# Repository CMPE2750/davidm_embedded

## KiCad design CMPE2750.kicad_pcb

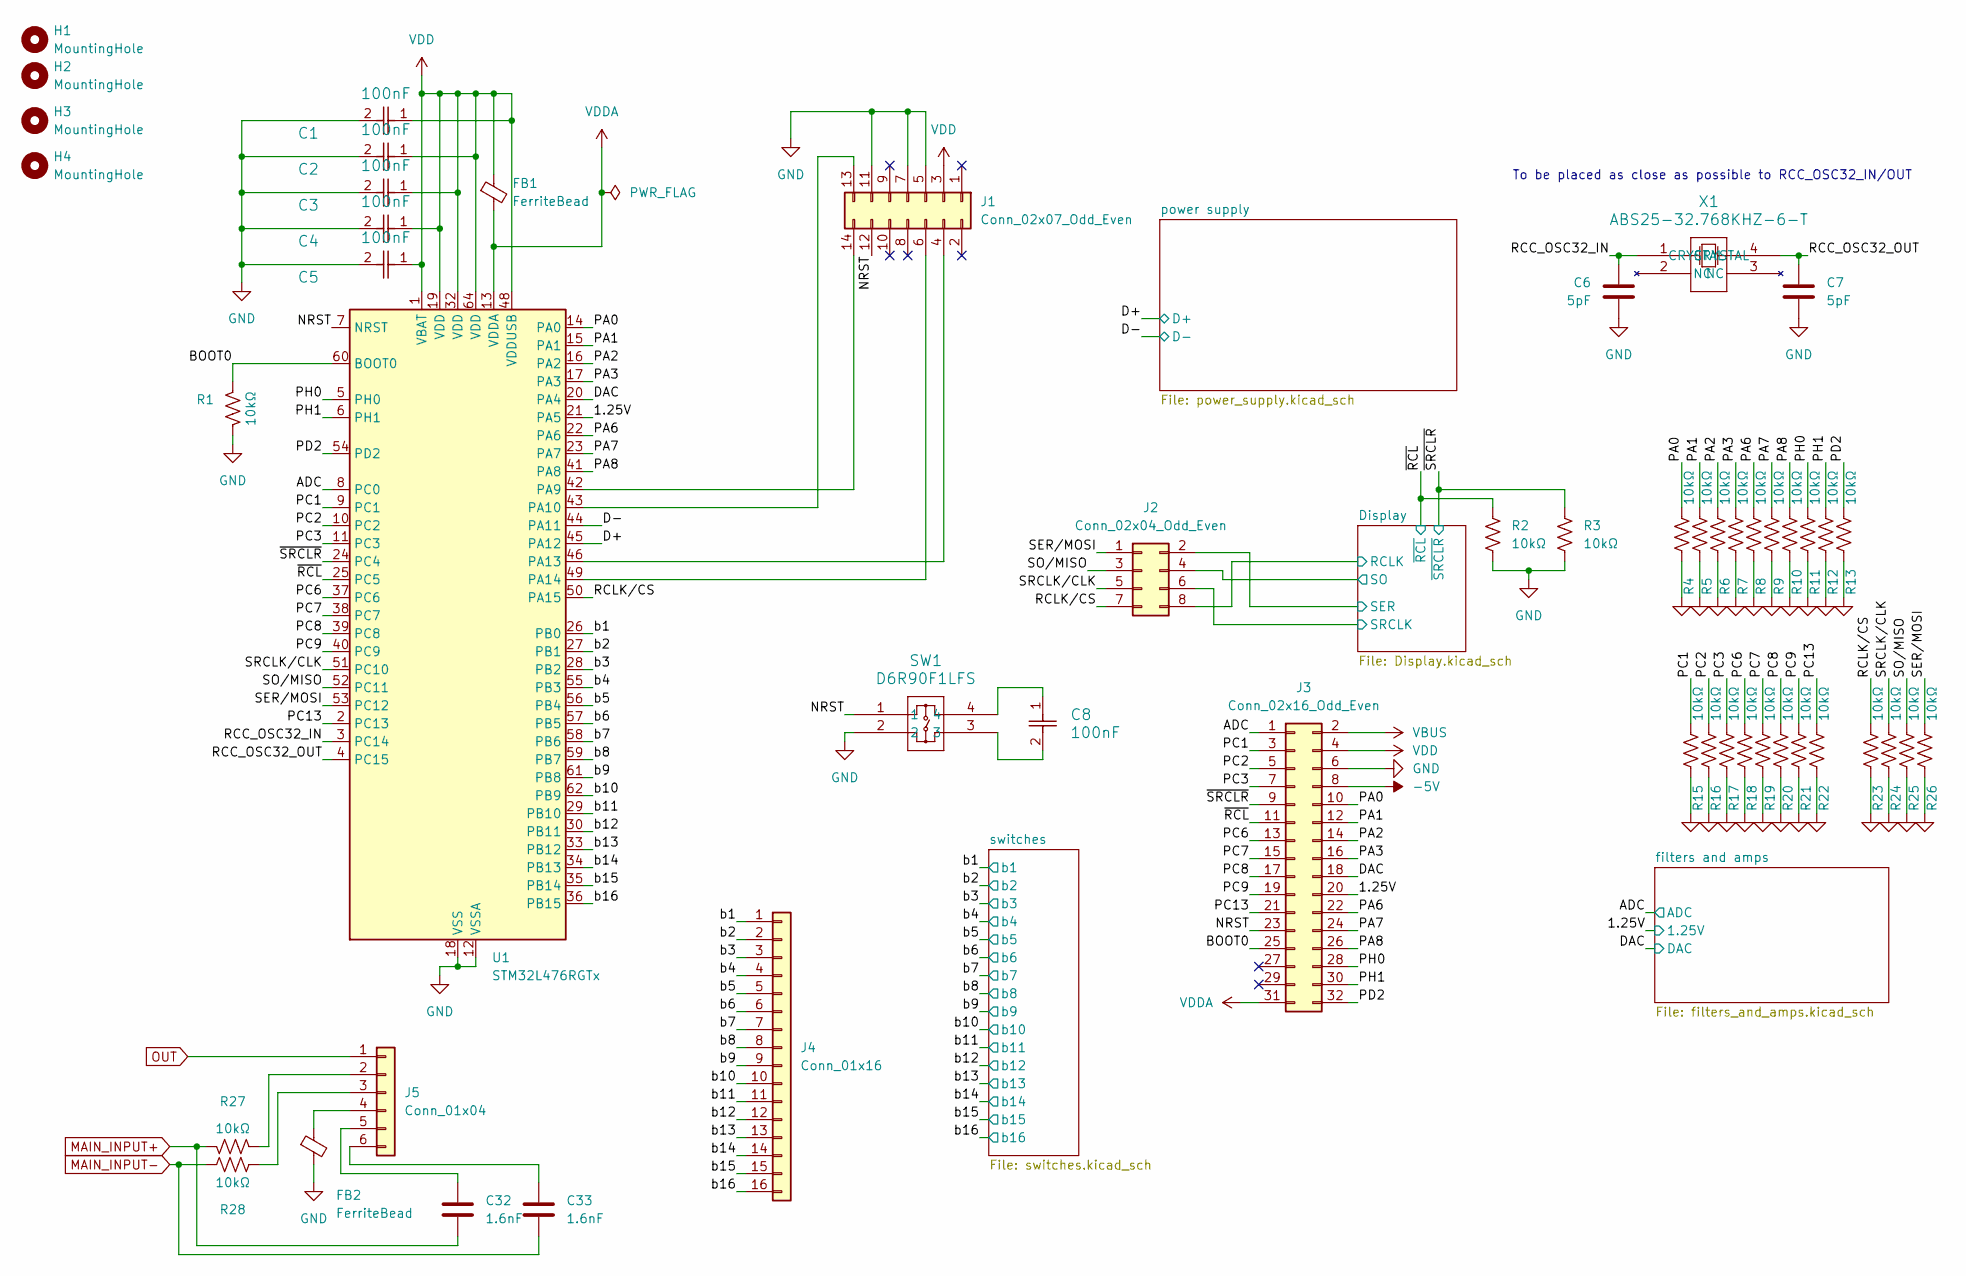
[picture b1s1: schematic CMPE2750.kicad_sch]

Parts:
C1, C2, C3, C4, C5, C8: 100nF; C_0402_1005Metric
C6, C7: 5pF; C_0402_1005Metric
C32, C33: 1.6nF; C_0805_2012Metric
FB1, FB2: FerriteBead; L_0603_1608Metric
H1, H2, H3, H4: MountingHole; MountingHole_3.2mm_M3
J1: Conn_02x07_Odd_Even; CONN_FTSH-107-01-F-DV-K-P-TR_SAI
J2: Conn_02x04_Odd_Even; PinHeader_2x04_P2.54mm_Vertical
J3: Conn_02x16_Odd_Even; PinHeader_2x16_P2.54mm_Vertical
J4: Conn_01x16; PinHeader_1x16_P2.54mm_Vertical
J5: Conn_01x04; PinHeader_1x06_P2.54mm_Vertical
R1, R2, R3, R4, R5, R6, R7, R8, R9, R10, R11, R12, R13, R15, R16, R17, R18, R19, R20, R21, R22, R23, R24, R25, R26, R27, R28: 10kΩ; R_0402_1005Metric
SW1: D6R90F1LFS; D6R_CNK
U1: STM32L476RGTx; LQFP-64_10x10mm_P0.5mm
X1: ABS25-32.768KHZ-6-T; X_ABS25_ABR

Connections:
-5V: J3.8; also elsewhere on the board
/1.25V: J3.20, U1.21 (PA5); also elsewhere on the board
/ADC: J3.1, U1.8 (PC0); also elsewhere on the board
/BOOT0: J3.25, R1.1, U1.60 (BOOT0)
/D+: U1.45 (PA12); also elsewhere on the board
/D-: U1.44 (PA11); also elsewhere on the board
/DAC: J3.18, U1.20 (PA4); also elsewhere on the board
/Display/RCLK: J2.8; also elsewhere on the board
/Display/SER: J2.2; also elsewhere on the board
/Display/SO: J2.4; also elsewhere on the board
/Display/SRCLK: J2.6; also elsewhere on the board
/NRST: J1.12, J3.23, SW1.1, U1.7 (NRST)
/PA0: J3.10, R4.1, U1.14 (PA0)
/PA1: J3.12, R5.1, U1.15 (PA1)
/PA2: J3.14, R6.1, U1.16 (PA2)
/PA3: J3.16, R7.1, U1.17 (PA3)
/PA6: J3.22, R8.1, U1.22 (PA6)
/PA7: J3.24, R9.1, U1.23 (PA7)
/PA8: J3.26, R10.1, U1.41 (PA8)
/PC1: J3.3, R15.1, U1.9 (PC1)
/PC2: J3.5, R16.1, U1.10 (PC2)
/PC3: J3.7, R17.1, U1.11 (PC3)
/PC6: J3.13, R18.1, U1.37 (PC6)
/PC7: J3.15, R19.1, U1.38 (PC7)
/PC8: J3.17, R20.1, U1.39 (PC8)
/PC9: J3.19, R21.1, U1.40 (PC9)
/PC13: J3.21, R22.1, U1.2 (PC13)
/PD2: J3.32, R13.1, U1.54 (PD2)
/PH0: J3.28, R11.1, U1.5 (PH0)
/PH1: J3.30, R12.1, U1.6 (PH1)
/RCC_OSC32_IN: C6.1, U1.3 (PC14), X1.1 (CRYSTAL)
/RCC_OSC32_OUT: C7.1, U1.4 (PC15), X1.4 (CRYSTAL)
/RCLK/CS: J2.7, R23.1, U1.50 (PA15)
/SER/MOSI: J2.1, R26.1, U1.53 (PC12)
/SO/MISO: J2.3, R25.1, U1.52 (PC11)
/SRCLK/CLK: J2.5, R24.1, U1.51 (PC10)
/b1: J4.1, U1.26 (PB0); also elsewhere on the board
/b2: J4.2, U1.27 (PB1); also elsewhere on the board
/b3: J4.3, U1.28 (PB2); also elsewhere on the board
/b4: J4.4, U1.55 (PB3); also elsewhere on the board
/b5: J4.5, U1.56 (PB4); also elsewhere on the board
/b6: J4.6, U1.57 (PB5); also elsewhere on the board
/b7: J4.7, U1.58 (PB6); also elsewhere on the board
/b8: J4.8, U1.59 (PB7); also elsewhere on the board
/b9: J4.9, U1.61 (PB8); also elsewhere on the board
/b10: J4.10, U1.62 (PB9); also elsewhere on the board
/b11: J4.11, U1.29 (PB10); also elsewhere on the board
/b12: J4.12, U1.30 (PB11); also elsewhere on the board
/b13: J4.13, U1.33 (PB12); also elsewhere on the board
/b14: J4.14, U1.34 (PB13); also elsewhere on the board
/b15: J4.15, U1.35 (PB14); also elsewhere on the board
/b16: J4.16, U1.36 (PB15); also elsewhere on the board
/~RCL: J3.11, R2.1, U1.25 (PC5); also elsewhere on the board
/~SRCLR: J3.9, R3.1, U1.24 (PC4); also elsewhere on the board
GND: C1.2, C2.2, C3.2, C4.2, C5.2, C6.2, C7.2, FB2.2, J1.5, J1.7, J1.11, J3.6, R1.2, R2.2, R3.2, R4.2, R5.2, R6.2, R7.2, R8.2, R9.2, R10.2, R11.2, R12.2, R13.2, R15.2, R16.2, R17.2, R18.2, R19.2, R20.2, R21.2, R22.2, R23.2, R24.2, R25.2, R26.2, SW1.2, U1.12 (VSSA), U1.18 (VSS), U1.31 (VSS), U1.47 (VSS), U1.63 (VSS); also elsewhere on the board
MAIN_INPUT+: C32.1, R27.1; also elsewhere on the board
MAIN_INPUT-: C33.1, R28.1; also elsewhere on the board
unnamed: C8.1, SW1.4
unnamed: C8.2, SW1.3
unnamed: J1.4, U1.46 (PA13)
unnamed: J1.6, U1.49 (PA14)
unnamed: J1.13, U1.43 (PA10)
unnamed: J1.14, U1.42 (PA9)
unnamed: J5.2, R27.2
unnamed: J5.3, R28.2
unnamed: FB2.1, J5.4
unnamed: C32.2, J5.5
unnamed: C33.2, J5.6
OUT: J5.1; also elsewhere on the board
VBUS: J3.2; also elsewhere on the board
VDD: C1.1, C2.1, C3.1, C4.1, C5.1, FB1.1, J1.3, J3.4, U1.1 (VBAT), U1.19 (VDD), U1.32 (VDD), U1.48 (VDDUSB), U1.64 (VDD); also elsewhere on the board
VDDA: FB1.2, J3.31, U1.13 (VDDA)

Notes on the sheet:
To be placed as close as possible to RCC_OSC32_IN/OUT

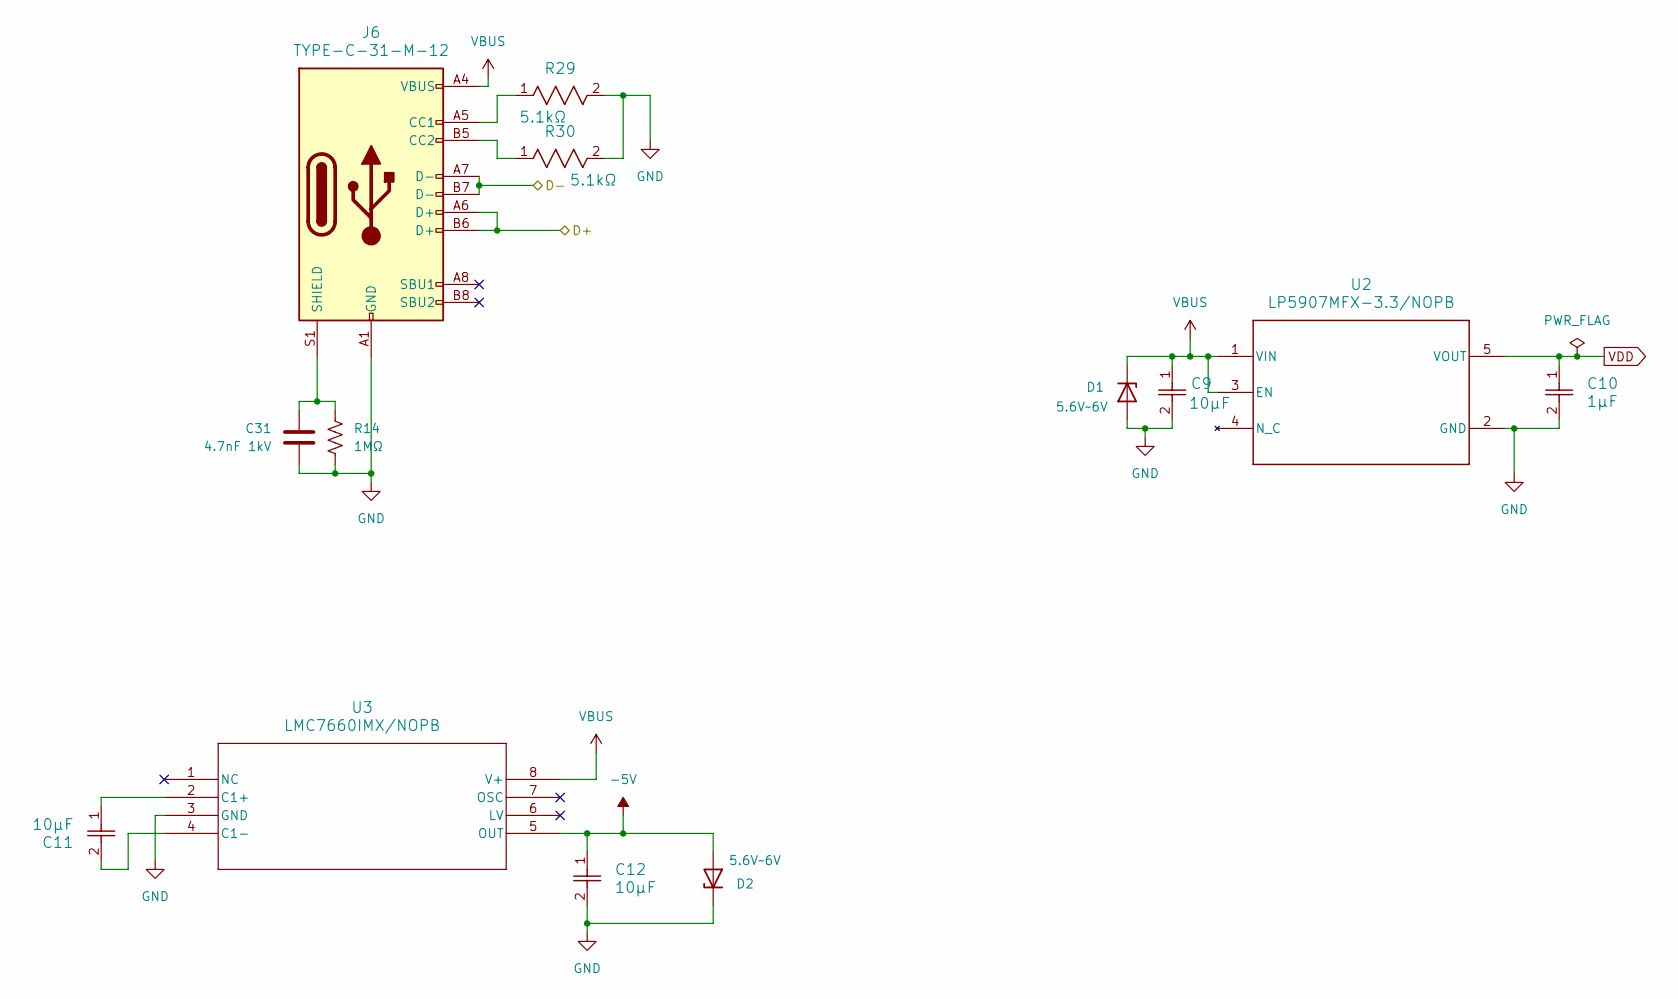
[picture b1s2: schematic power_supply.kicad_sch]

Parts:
C9, C11, C12: 10µF; C_1206_3216Metric
C10: 1µF; C_1206_3216Metric
C31: 4.7nF 1kV; C_1206_3216Metric
D1, D2: 5.6V~6V; D_SOD-123
J6: TYPE-C-31-M-12; USB_C_Receptacle_HRO_TYPE-C-31-M-12
R14: 1MΩ; R_2512_6332Metric
R29, R30: 5.1kΩ; R_0603_1608Metric
U2: LP5907MFX-3.3/NOPB; DBV0005A_N
U3: LMC7660IMX/NOPB; SOIC-8_3.9x4.9mm_P1.27mm

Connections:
-5V: C12.1, D2.2 (A), U3.5 (OUT); also elsewhere on the board
/D+: J6.A6 (D+), J6.B6 (D+); also elsewhere on the board
/D-: J6.A7 (D-), J6.B7 (D-); also elsewhere on the board
GND: C9.2, C10.2, C12.2, C31.2, D1.2 (A), D2.1 (K), J6.A1 (GND), J6.A12 (GND), J6.B1 (GND), J6.B12 (GND), R14.2, R29.2, R30.2, U2.2 (GND), U3.3 (GND); also elsewhere on the board
unnamed: J6.A5 (CC1), R29.1
unnamed: J6.B5 (CC2), R30.1
unnamed: C31.1, J6.S1 (SHIELD), R14.1
unnamed: C11.1, U3.2 (C1+)
unnamed: C11.2, U3.4 (C1-)
VBUS: C9.1, D1.1 (K), J6.A4 (VBUS), J6.A9 (VBUS), J6.B4 (VBUS), J6.B9 (VBUS), U2.1 (VIN), U2.3 (EN), U3.8 (V+); also elsewhere on the board
VDD: C10.1, U2.5 (VOUT); also elsewhere on the board

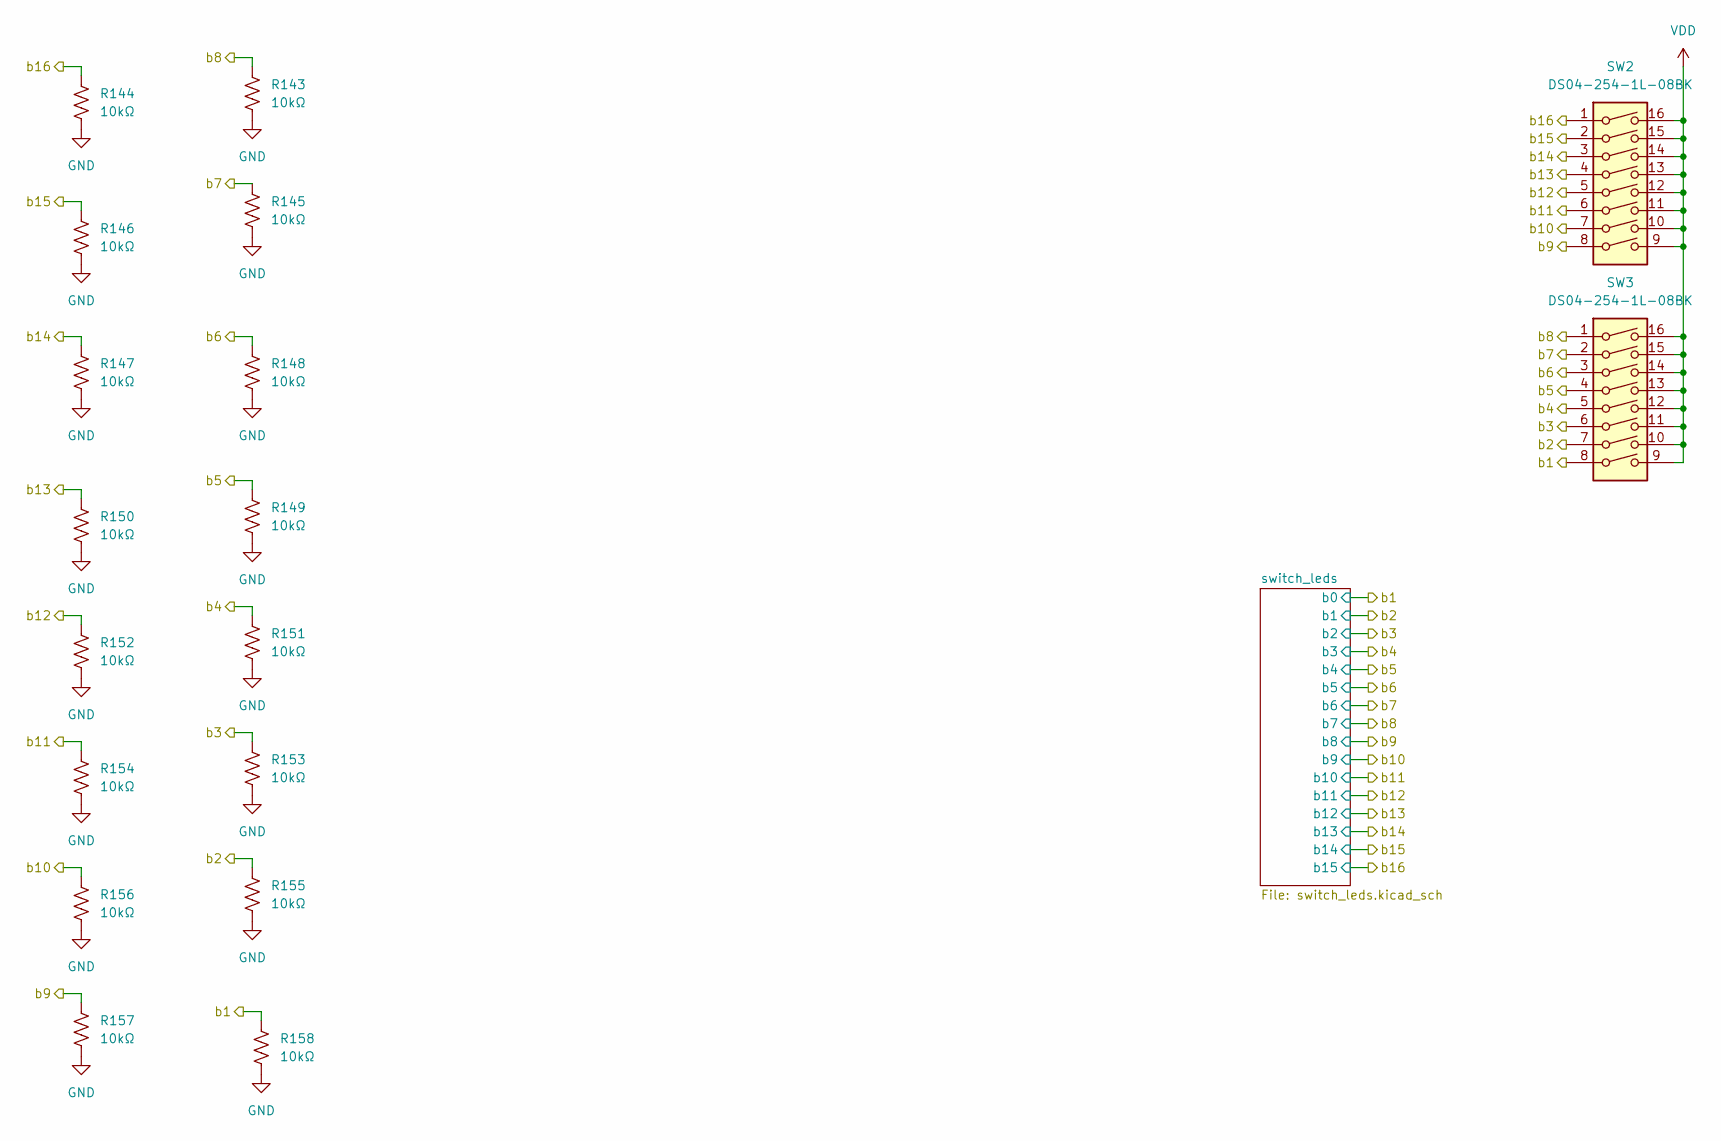
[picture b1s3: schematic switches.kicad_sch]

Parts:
R143, R144, R145, R146, R147, R148, R149, R150, R151, R152, R153, R154, R155, R156, R157, R158: 10kΩ; R_0402_1005Metric
SW2, SW3: DS04-254-1L-08BK; DIP-16_W7.62mm

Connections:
/b1: R158.1, SW3.8; also elsewhere on the board
/b2: R155.1, SW3.7; also elsewhere on the board
/b3: R153.1, SW3.6; also elsewhere on the board
/b4: R151.1, SW3.5; also elsewhere on the board
/b5: R149.1, SW3.4; also elsewhere on the board
/b6: R148.1, SW3.3; also elsewhere on the board
/b7: R145.1, SW3.2; also elsewhere on the board
/b8: R143.1, SW3.1; also elsewhere on the board
/b9: R157.1, SW2.8; also elsewhere on the board
/b10: R156.1, SW2.7; also elsewhere on the board
/b11: R154.1, SW2.6; also elsewhere on the board
/b12: R152.1, SW2.5; also elsewhere on the board
/b13: R150.1, SW2.4; also elsewhere on the board
/b14: R147.1, SW2.3; also elsewhere on the board
/b15: R146.1, SW2.2; also elsewhere on the board
/b16: R144.1, SW2.1; also elsewhere on the board
GND: R143.2, R144.2, R145.2, R146.2, R147.2, R148.2, R149.2, R150.2, R151.2, R152.2, R153.2, R154.2, R155.2, R156.2, R157.2, R158.2; also elsewhere on the board
VDD: SW2.9, SW2.10, SW2.11, SW2.12, SW2.13, SW2.14, SW2.15, SW2.16, SW3.9, SW3.10, SW3.11, SW3.12, SW3.13, SW3.14, SW3.15, SW3.16; also elsewhere on the board

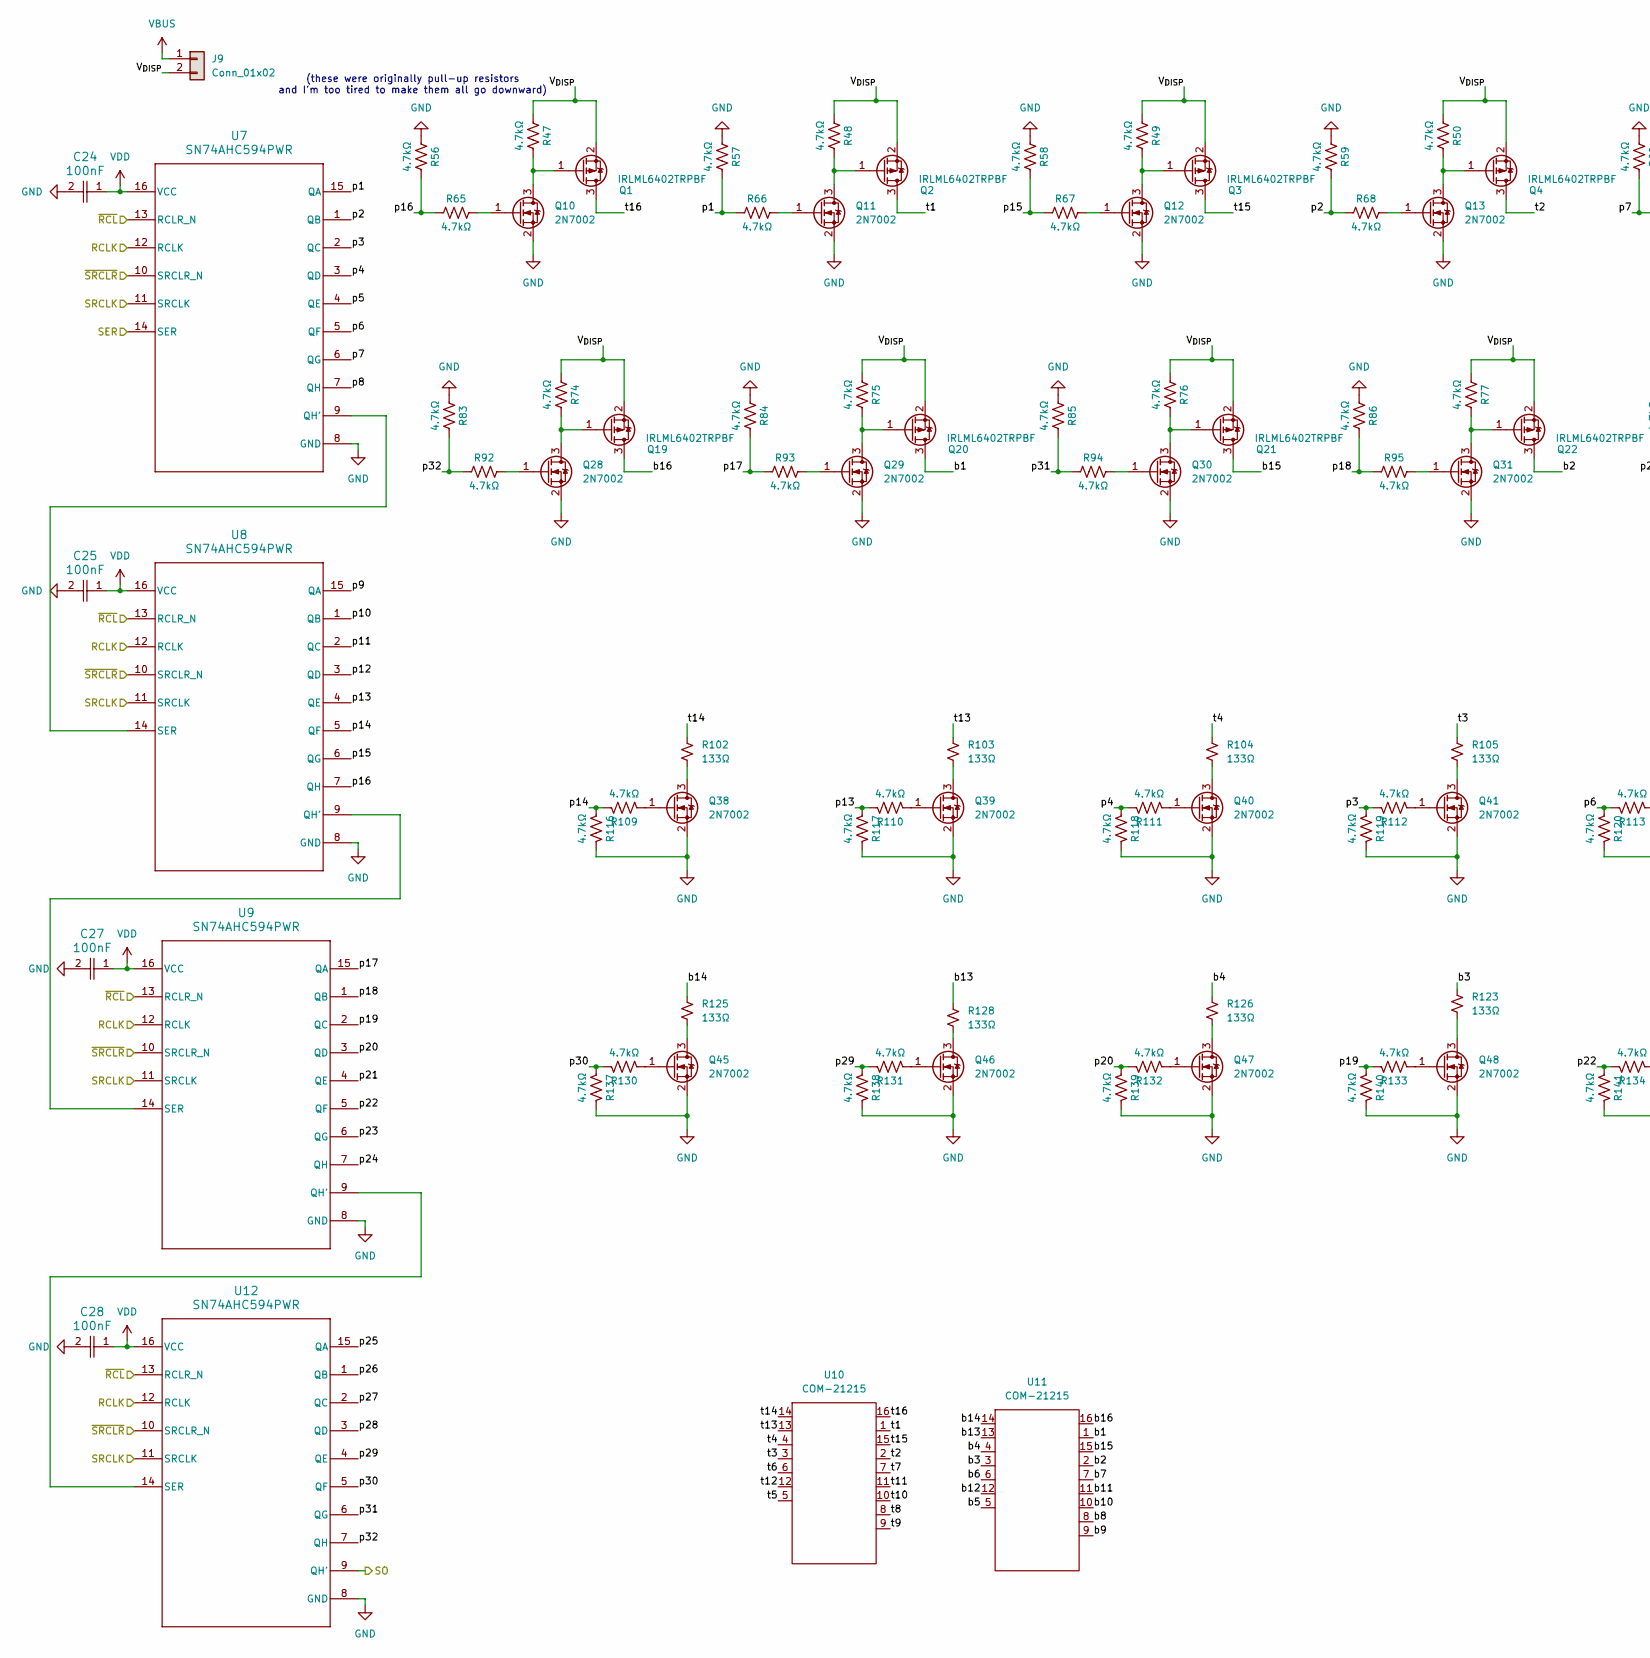
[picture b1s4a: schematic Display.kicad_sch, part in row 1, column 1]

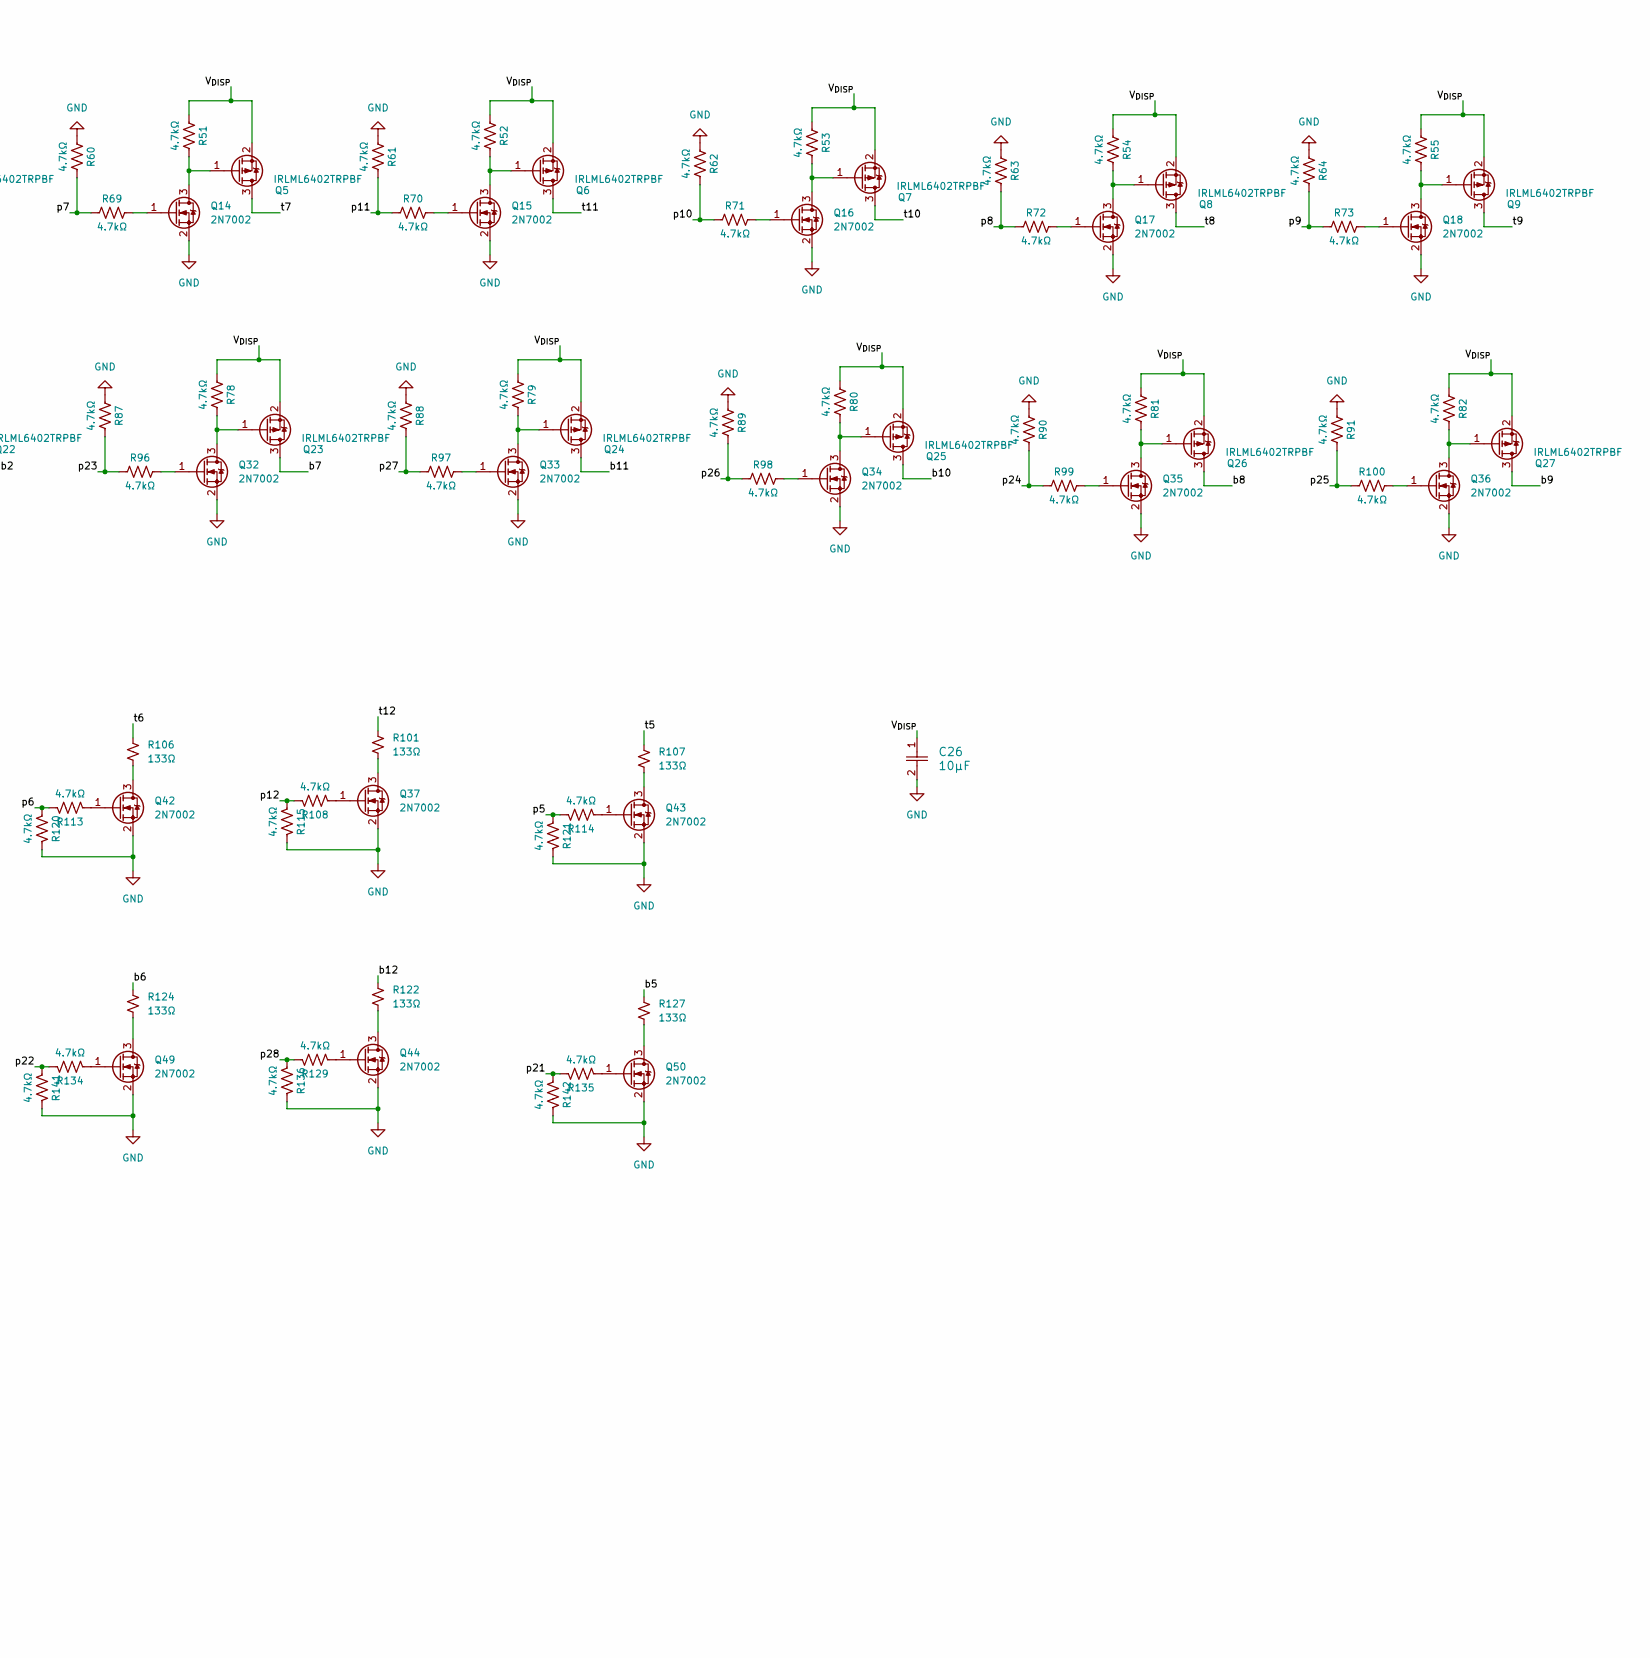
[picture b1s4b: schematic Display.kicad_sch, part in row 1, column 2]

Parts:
C24, C25, C27, C28: 100nF; C_0402_1005Metric
C26: 10µF; C_1206_3216Metric
J9: Conn_01x02; PinHeader_1x02_P2.54mm_Vertical
Q1, Q2, Q3, Q4, Q5, Q6, Q7, Q8, Q9, Q19, Q20, Q21, Q22, Q23, Q24, Q25, Q26, Q27: IRLML6402TRPBF; SOT-23
Q10, Q11, Q12, Q13, Q14, Q15, Q16, Q17, Q18, Q28, Q29, Q30, Q31, Q32, Q33, Q34, Q35, Q36, Q37, Q38, Q39, Q40, Q41, Q42, Q43, Q44, Q45, Q46, Q47, Q48, Q49, Q50: 2N7002; SOT-23
R47, R48, R49, R50, R51, R52, R53, R54, R55, R56, R57, R58, R59, R60, R61, R62, R63, R64, R65, R66, R67, R68, R69, R70, R71, R72, R73, R74, R75, R76, R77, R78, R79, R80, R81, R82, R83, R84, R85, R86, R87, R88, R89, R90, R91, R92, R93, R94, R95, R96, R97, R98, R99, R100, R108, R109, R110, R111, R112, R113, R114, R115, R116, R117, R118, R119, R120, R121, R129, R130, R131, R132, R133, R134, R135, R136, R137, R138, R139, R140, R141, R142: 4.7kΩ; R_0402_1005Metric
R101, R102, R103, R104, R105, R106, R107, R122, R123, R124, R125, R126, R127, R128: 133Ω; R_0603_1608Metric
U7, U8, U9, U12: SN74AHC594PWR; TSSOP-16_4.4x5mm_P0.65mm
U10, U11: COM-21215

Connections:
/Display/RCLK: U7.12 (RCLK), U8.12 (RCLK), U9.12 (RCLK), U12.12 (RCLK); also elsewhere on the board
/Display/SER: U7.14 (SER); also elsewhere on the board
/Display/SO: U12.9 (QH'); also elsewhere on the board
/Display/SRCLK: U7.11 (SRCLK), U8.11 (SRCLK), U9.11 (SRCLK), U12.11 (SRCLK); also elsewhere on the board
/Display/V_{DISP}: C26.1, J9.2, Q1.2 (S), Q2.2 (S), Q3.2 (S), Q4.2 (S), Q5.2 (S), Q6.2 (S), Q7.2 (S), Q8.2 (S), Q9.2 (S), Q19.2 (S), Q20.2 (S), Q21.2 (S), Q22.2 (S), Q23.2 (S), Q24.2 (S), Q25.2 (S), Q26.2 (S), Q27.2 (S), R47.1, R48.1, R49.1, R50.1, R51.1, R52.1, R53.1, R54.1, R55.1, R74.1, R75.1, R76.1, R77.1, R78.1, R79.1, R80.1, R81.1, R82.1
/Display/b1: Q20.3 (D), U11.1
/Display/b2: Q22.3 (D), U11.2
/Display/b3: R123.1, U11.3
/Display/b4: R126.1, U11.4
/Display/b5: R127.1, U11.5
/Display/b6: R124.1, U11.6
/Display/b7: Q23.3 (D), U11.7
/Display/b8: Q26.3 (D), U11.8
/Display/b9: Q27.3 (D), U11.9
/Display/b10: Q25.3 (D), U11.10
/Display/b11: Q24.3 (D), U11.11
/Display/b12: R122.1, U11.12
/Display/b13: R128.1, U11.13
/Display/b14: R125.1, U11.14
/Display/b15: Q21.3 (D), U11.15
/Display/b16: Q19.3 (D), U11.16
/Display/p1: R57.2, R66.1, U7.15 (QA)
/Display/p2: R59.2, R68.1, U7.1 (QB)
/Display/p3: R112.1, R119.2, U7.2 (QC)
/Display/p4: R111.1, R118.2, U7.3 (QD)
/Display/p5: R114.1, R121.2, U7.4 (QE)
/Display/p6: R113.1, R120.2, U7.5 (QF)
/Display/p7: R60.2, R69.1, U7.6 (QG)
/Display/p8: R63.2, R72.1, U7.7 (QH)
/Display/p9: R64.2, R73.1, U8.15 (QA)
/Display/p10: R62.2, R71.1, U8.1 (QB)
/Display/p11: R61.2, R70.1, U8.2 (QC)
/Display/p12: R108.1, R115.2, U8.3 (QD)
/Display/p13: R110.1, R117.2, U8.4 (QE)
/Display/p14: R109.1, R116.2, U8.5 (QF)
/Display/p15: R58.2, R67.1, U8.6 (QG)
/Display/p16: R56.2, R65.1, U8.7 (QH)
/Display/p17: R84.2, R93.1, U9.15 (QA)
/Display/p18: R86.2, R95.1, U9.1 (QB)
/Display/p19: R133.1, R140.2, U9.2 (QC)
/Display/p20: R132.1, R139.2, U9.3 (QD)
/Display/p21: R135.1, R142.2, U9.4 (QE)
/Display/p22: R134.1, R141.2, U9.5 (QF)
/Display/p23: R87.2, R96.1, U9.6 (QG)
/Display/p24: R90.2, R99.1, U9.7 (QH)
/Display/p25: R91.2, R100.1, U12.15 (QA)
/Display/p26: R89.2, R98.1, U12.1 (QB)
/Display/p27: R88.2, R97.1, U12.2 (QC)
/Display/p28: R129.1, R136.2, U12.3 (QD)
/Display/p29: R131.1, R138.2, U12.4 (QE)
/Display/p30: R130.1, R137.2, U12.5 (QF)
/Display/p31: R85.2, R94.1, U12.6 (QG)
/Display/p32: R83.2, R92.1, U12.7 (QH)
/Display/t1: Q2.3 (D), U10.1
/Display/t2: Q4.3 (D), U10.2
/Display/t3: R105.1, U10.3
/Display/t4: R104.1, U10.4
/Display/t5: R107.1, U10.5
/Display/t6: R106.1, U10.6
/Display/t7: Q5.3 (D), U10.7
/Display/t8: Q8.3 (D), U10.8
/Display/t9: Q9.3 (D), U10.9
/Display/t10: Q7.3 (D), U10.10
/Display/t11: Q6.3 (D), U10.11
/Display/t12: R101.1, U10.12
/Display/t13: R103.1, U10.13
/Display/t14: R102.1, U10.14
/Display/t15: Q3.3 (D), U10.15
/Display/t16: Q1.3 (D), U10.16
/~RCL: U7.13 (RCLR_N), U8.13 (RCLR_N), U9.13 (RCLR_N), U12.13 (RCLR_N); also elsewhere on the board
/~SRCLR: U7.10 (SRCLR_N), U8.10 (SRCLR_N), U9.10 (SRCLR_N), U12.10 (SRCLR_N); also elsewhere on the board
GND: C24.2, C25.2, C26.2, C27.2, C28.2, Q10.2 (S), Q11.2 (S), Q12.2 (S), Q13.2 (S), Q14.2 (S), Q15.2 (S), Q16.2 (S), Q17.2 (S), Q18.2 (S), Q28.2 (S), Q29.2 (S), Q30.2 (S), Q31.2 (S), Q32.2 (S), Q33.2 (S), Q34.2 (S), Q35.2 (S), Q36.2 (S), Q37.2 (S), Q38.2 (S), Q39.2 (S), Q40.2 (S), Q41.2 (S), Q42.2 (S), Q43.2 (S), Q44.2 (S), Q45.2 (S), Q46.2 (S), Q47.2 (S), Q48.2 (S), Q49.2 (S), Q50.2 (S), R56.1, R57.1, R58.1, R59.1, R60.1, R61.1, R62.1, R63.1, R64.1, R83.1, R84.1, R85.1, R86.1, R87.1, R88.1, R89.1, R90.1, R91.1, R115.1, R116.1, R117.1, R118.1, R119.1, R120.1, R121.1, R136.1, R137.1, R138.1, R139.1, R140.1, R141.1, R142.1, U7.8 (GND), U8.8 (GND), U9.8 (GND), U12.8 (GND); also elsewhere on the board
unnamed: Q1.1 (G), Q10.3 (D), R47.2
unnamed: Q10.1 (G), R65.2
unnamed: Q2.1 (G), Q11.3 (D), R48.2
unnamed: Q11.1 (G), R66.2
unnamed: Q3.1 (G), Q12.3 (D), R49.2
unnamed: Q12.1 (G), R67.2
unnamed: Q4.1 (G), Q13.3 (D), R50.2
unnamed: Q13.1 (G), R68.2
unnamed: Q5.1 (G), Q14.3 (D), R51.2
unnamed: Q14.1 (G), R69.2
unnamed: Q6.1 (G), Q15.3 (D), R52.2
unnamed: Q15.1 (G), R70.2
unnamed: Q7.1 (G), Q16.3 (D), R53.2
unnamed: Q16.1 (G), R71.2
unnamed: Q8.1 (G), Q17.3 (D), R54.2
unnamed: Q17.1 (G), R72.2
unnamed: Q9.1 (G), Q18.3 (D), R55.2
unnamed: Q18.1 (G), R73.2
unnamed: Q19.1 (G), Q28.3 (D), R74.2
unnamed: Q20.1 (G), Q29.3 (D), R75.2
unnamed: Q21.1 (G), Q30.3 (D), R76.2
unnamed: Q22.1 (G), Q31.3 (D), R77.2
unnamed: Q23.1 (G), Q32.3 (D), R78.2
unnamed: Q24.1 (G), Q33.3 (D), R79.2
unnamed: Q25.1 (G), Q34.3 (D), R80.2
unnamed: Q26.1 (G), Q35.3 (D), R81.2
unnamed: Q27.1 (G), Q36.3 (D), R82.2
unnamed: Q28.1 (G), R92.2
unnamed: Q29.1 (G), R93.2
unnamed: Q30.1 (G), R94.2
unnamed: Q31.1 (G), R95.2
unnamed: Q32.1 (G), R96.2
unnamed: Q33.1 (G), R97.2
unnamed: Q34.1 (G), R98.2
unnamed: Q35.1 (G), R99.2
unnamed: Q36.1 (G), R100.2
unnamed: Q37.3 (D), R101.2
unnamed: Q37.1 (G), R108.2
unnamed: Q38.3 (D), R102.2
unnamed: Q38.1 (G), R109.2
unnamed: Q39.3 (D), R103.2
unnamed: Q39.1 (G), R110.2
unnamed: Q40.3 (D), R104.2
unnamed: Q40.1 (G), R111.2
unnamed: Q41.3 (D), R105.2
unnamed: Q41.1 (G), R112.2
unnamed: Q42.3 (D), R106.2
unnamed: Q42.1 (G), R113.2
unnamed: Q43.3 (D), R107.2
unnamed: Q43.1 (G), R114.2
unnamed: Q44.3 (D), R122.2
unnamed: Q44.1 (G), R129.2
unnamed: Q45.3 (D), R125.2
unnamed: Q45.1 (G), R130.2
unnamed: Q46.3 (D), R128.2
unnamed: Q46.1 (G), R131.2
unnamed: Q47.3 (D), R126.2
unnamed: Q47.1 (G), R132.2
unnamed: Q48.3 (D), R123.2
unnamed: Q48.1 (G), R133.2
unnamed: Q49.3 (D), R124.2
unnamed: Q49.1 (G), R134.2
unnamed: Q50.3 (D), R127.2
unnamed: Q50.1 (G), R135.2
unnamed: U7.9 (QH'), U8.14 (SER)
unnamed: U8.9 (QH'), U9.14 (SER)
unnamed: U9.9 (QH'), U12.14 (SER)
VBUS: J9.1; also elsewhere on the board
VDD: C24.1, C25.1, C27.1, C28.1, U7.16 (VCC), U8.16 (VCC), U9.16 (VCC), U12.16 (VCC); also elsewhere on the board

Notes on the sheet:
(these were originally pull-up resistors and I'm too tired to make them all go downward)
